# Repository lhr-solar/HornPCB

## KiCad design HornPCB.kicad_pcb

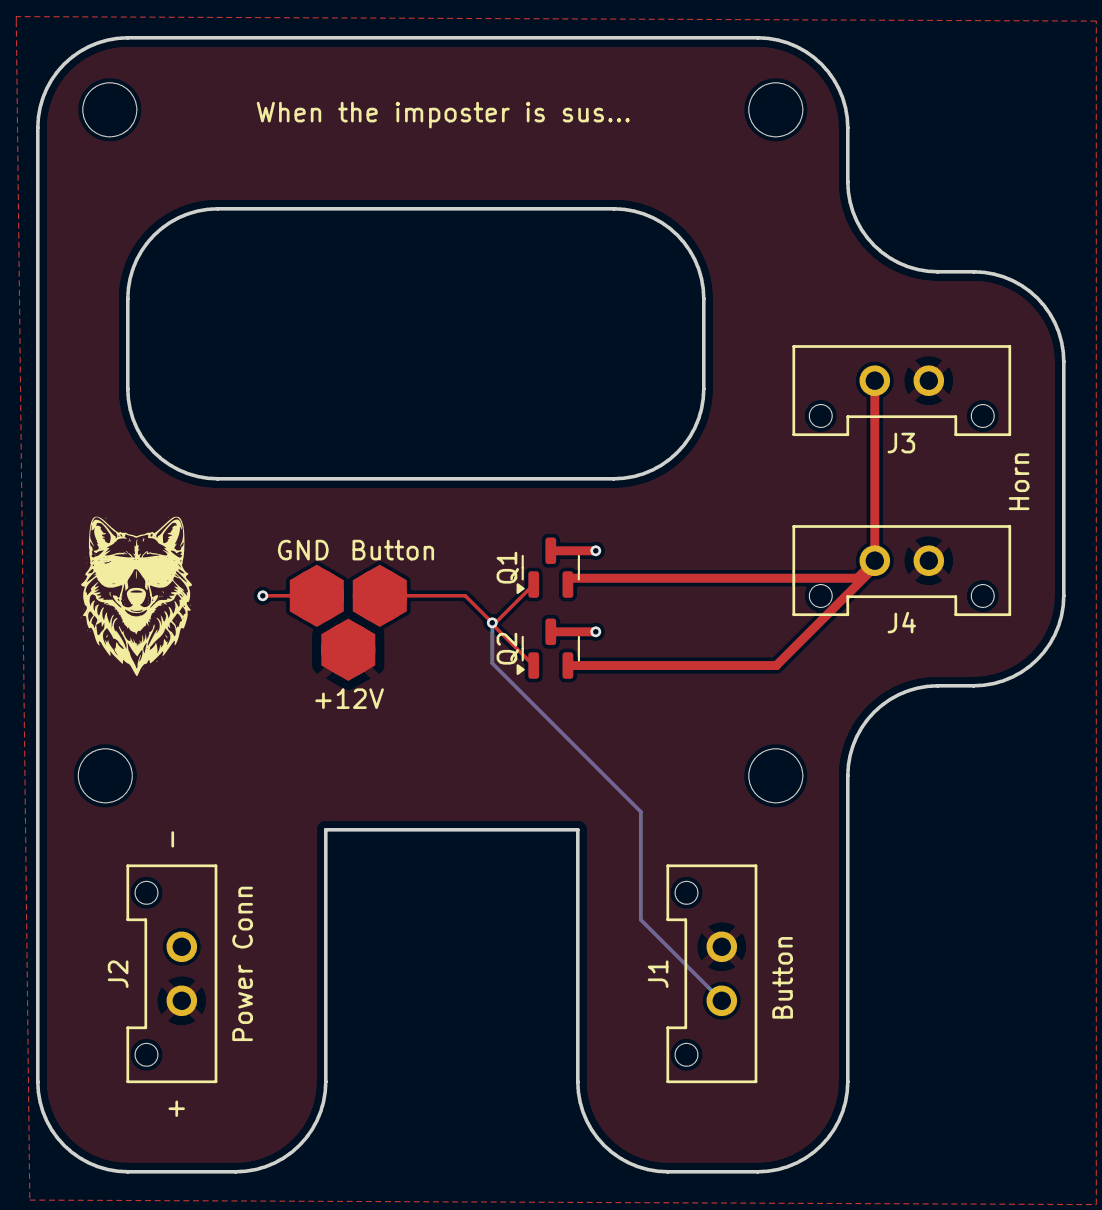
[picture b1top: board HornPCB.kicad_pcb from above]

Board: 2 copper layers, 57.0 x 63.0 mm, 9 parts (0 on the bottom side), 4 nets.

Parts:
+12V: TestPoint; TestPoint_HEX_3mmID
Button: TestPoint; TestPoint_HEX_3mmID
GND: TestPoint; TestPoint_HEX_3mmID
J1, J2, J3, J4: Conn_01x02; Molex_MicroFit3.0_1x2xP3.00mm_PolarizingPeg_Vertical
Q1, Q2: IRLML0030; SOT-23

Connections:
+12V: +12V.1, J1.2, J2.1, J3.1, J4.1
/HORN_SIG: Button.1, J1.1, Q1.1 (G), Q2.1 (G)
GND: GND.1, J2.2, Q1.3 (D), Q2.3 (D)
unnamed: J3.2, J4.2, Q1.2 (S), Q2.2 (S)

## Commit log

2024-11-07 added .gitignore
2024-11-07 trace fix
